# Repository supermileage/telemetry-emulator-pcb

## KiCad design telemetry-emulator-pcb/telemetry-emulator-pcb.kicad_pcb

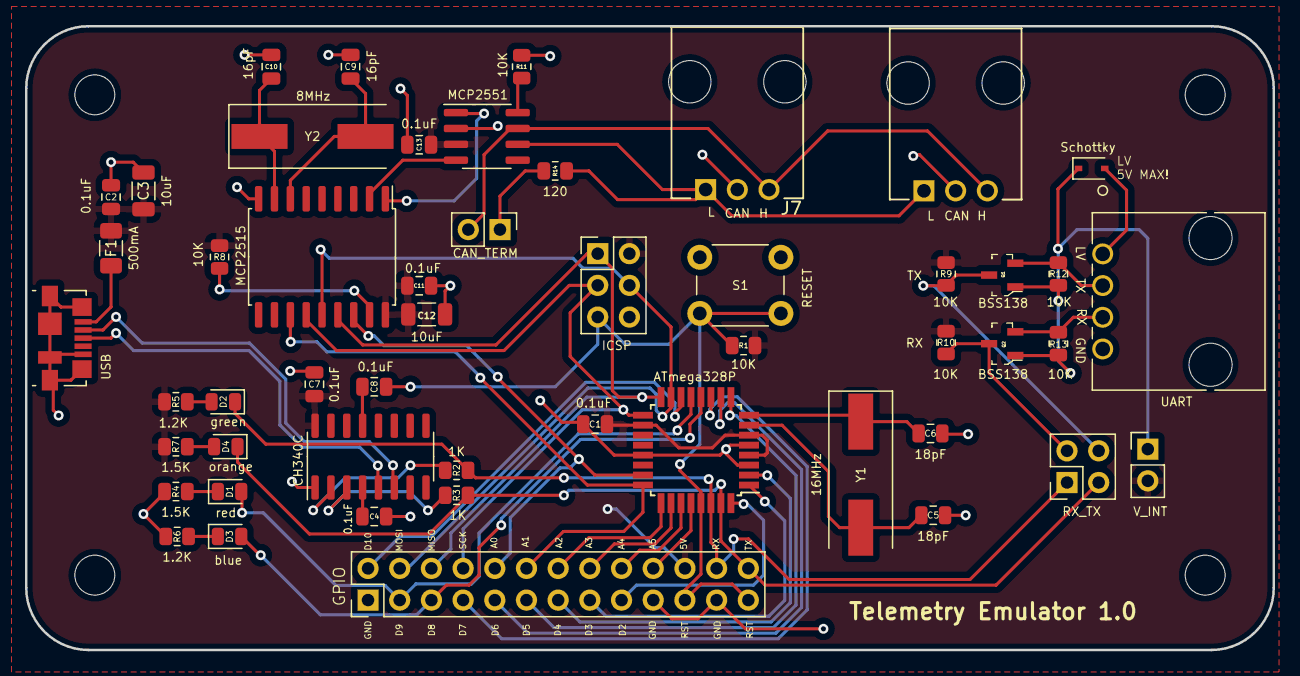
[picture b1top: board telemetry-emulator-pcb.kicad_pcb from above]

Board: 2 copper layers, 100.0 x 50.0 mm, 55 parts (0 on the bottom side), 51 nets.

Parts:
C1, C2, C4, C7, C8, C11, C13: 0.1uF; C_0805_2012Metric
C3, C12: 10uF; C_1206_3216Metric
C5, C6: 18pF; C_0805_2012Metric
C9, C10: 16pF; C_0805_2012Metric
D1: red; LED_0805_2012Metric
D2: green; LED_0805_2012Metric
D3: blue; LED_0805_2012Metric
D4: orange; LED_0805_2012Metric
D5: Schottky; D_SOD-323
F1: 500mA; Fuse_1206_3216Metric
H1: ICSP; PinHeader_2x03_P2.54mm_Vertical
H2, H3, H4, H5: MountingHole; MountingHole_3.2mm_M3
IC1: ATmega328P; TQFP-32_7x7mm_P0.8mm
IC2: MCP2515; SOIC-18W_7.5x11.6mm_P1.27mm
IC3: MCP2551; SOIC-8_3.9x4.9mm_P1.27mm
J1: USB; USB_Micro-B_Molex_47346-0001
J2: RX_TX; PinHeader_2x02_P2.54mm_Vertical
J3: GPIO; PinHeader_2x13_P2.54mm_Vertical
J4: CAN_TERM; PinHeader_1x02_P2.54mm_Vertical
J5: V_INT; PinHeader_1x02_P2.54mm_Vertical
J6: UART; molex_sl_1x04_horizontal
J7, J8: CAN; molex-sl-1x03-horizontal
Q1, Q2: BSS138; SOT-23-3
R1, R8, R9, R10, R11, R12, R13: 10K; R_0805_2012Metric
R2, R3: 1K; R_0805_2012Metric
R4, R7: 1.5K; R_0805_2012Metric
R5, R6: 1.2K; R_0805_2012Metric
R14: 120; R_0805_2012Metric
S1: RESET; SW_PUSH_6mm
U1: CH340C; SOIC-16_3.9x9.9mm_P1.27mm
Y1: 16MHz; Crystal_SMD_HC49-SD
Y2: 8MHz; Crystal_SMD_HC49-SD

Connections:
+5V: C1.1, C2.2, C3.1, C7.1, C11.1, C12.1, C13.1, F1.2, H1.2, IC1.4 (VCC), IC1.6 (VCC), IC1.18 (AVCC), IC2.18 (VDD), IC3.3 (VDD), J3.22, J5.2, R1.1, R5.1, R7.1, R8.2, R9.1, R10.1, U1.16 (VCC)
A2: IC1.25 (PC2), J3.14
A3: IC1.26 (PC3), J3.16
A4: IC1.27 (PC4), J3.18
A5: IC1.28 (PC5), J3.20
CANH: IC3.7 (CANH), J4.2, J7.3, J8.3
CANL: IC3.6 (CANL), J7.1, J8.1, R14.2
CAN_CS: IC1.23 (PC0), IC2.16 (~CS), J3.10
CAN_INT: IC1.24 (PC1), IC2.12 (~INT), J3.12
D2: IC1.32 (PD2), J3.17
D3: IC1.1 (PD3), J3.15
D4: IC1.2 (PD4), J3.13
D5: IC1.9 (PD5), J3.11
D6: IC1.10 (PD6), J3.9
D7: IC1.11 (PD7), J3.7
D8: D3.2 (A), IC1.12 (PB0), J3.5
D9: D1.2 (A), IC1.13 (PB1), J3.3
D10: IC1.14 (PB2), J3.2
Earth: C1.2, C2.1, C3.2, C4.1, C5.2, C6.2, C7.2, C9.2, C10.2, C11.2, C12.2, C13.2, H1.6, IC1.3 (GND), IC1.5 (GND), IC1.21 (GND), IC2.9 (VSS), IC3.2 (VSS), J1.5 (GND), J1.6 (Shield), J3.1, J3.19, J3.23, J6.4, J7.2, J8.2, R4.1, R6.1, R11.1, S1.1, U1.1 (GND)
MISO: H1.1, IC1.16 (PB4), IC2.15 (SO), J3.6
MOSI: H1.4, IC1.15 (PB3), IC2.14 (SI), J3.4
unnamed: C4.2, U1.4 (V3)
unnamed: C5.1, IC1.7 (XTAL1/PB6), Y1.2
unnamed: C6.1, IC1.8 (XTAL2/PB7), Y1.1
unnamed: C8.1, U1.13 (~DTR)
unnamed: C9.1, IC2.7 (OSC2), Y2.2
unnamed: C10.1, IC2.8 (OSC1), Y2.1
unnamed: D1.1 (K), R4.2
unnamed: D2.2 (A), R5.2
unnamed: D3.1 (K), R6.2
unnamed: D4.2 (A), R7.2
unnamed: D5.2 (A), J6.1
unnamed: F1.1, J1.1 (VBUS)
unnamed: IC2.1 (TXCAN), IC3.1 (TXD)
unnamed: IC2.2 (RXCAN), IC3.4 (RXD)
unnamed: IC2.17 (~RESET), R8.1
unnamed: IC3.8 (Rs), R11.2
unnamed: J1.2 (D-), U1.6 (UD-)
unnamed: J1.3 (D+), U1.5 (UD+)
unnamed: J4.1, R14.1
unnamed: R2.1, U1.2 (TXD)
unnamed: R3.2, U1.3 (RXD)
RX: J2.2, Q2.3 (D), R10.2
RX_EXT: J6.3, Q2.2 (S), R13.1
RX_USB: D2.1 (K), IC1.30 (PD0), J2.1, J3.24, R2.2
SCK: H1.3, IC1.17 (PB5), IC2.13 (SCK), J3.8
TX: J2.4, Q1.3 (D), R9.2
TX_EXT: J6.2, Q1.2 (S), R12.1
TX_USB: D4.1 (K), IC1.31 (PD1), J2.3, J3.26, R3.1
V_EXT: D5.1 (K), J5.1, Q1.1 (G), Q2.1 (G), R12.2, R13.2
reset: C8.2, H1.5, IC1.29 (~RESET/PC6), J3.21, J3.25, R1.2, S1.2

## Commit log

2022-08-18 Almost finished schematic design
2022-08-18 Connects rx/tx ext to UART connector
2022-08-24 First draft of telemetry-emulator-pcb complete
2022-08-24 Minor changes
2022-08-24 Adds tracks for gpio header
2022-08-24 Small change
2022-08-25 solves potential problem with bypassing logic level shifter
2022-08-25 done and done
2022-08-26 Rdy for review
2022-08-29 Board is finished
2022-08-29 adds rounded edges to pcb and modifies xtal resistance
2022-08-29 Final changes
2022-09-06 some small changes
2022-09-06 adds supermileage logo
2022-09-06 New changes
2022-09-06 makes supermilage logo a bit smaller
2022-09-20 fixes merge conflict
2022-10-30 Fixes reset issue
2022-11-17 Adds newest drill files
2022-11-21 adds minor changes to project
2022-11-22 Updates output files
2022-11-22 Gets rid of intermediate project folder

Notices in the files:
parts and their libraries:
Copyright 2021 Accelerated Designs. All rights reserved.
